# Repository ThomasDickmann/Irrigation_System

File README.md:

# Arduino Irrigation System - WIP
The purpose of this project was to learn basic electronic design, PCB layout, and embedded software development using VS code and PlatformIO.
The project is a work in progress, so use any code with appropriate caution!

Written in 2022 by Thomas Dickmann. 

## System architecture and intended use 
The goal is to create a fully automated irrigation system to be used in a home automation context. The hardware is capable of controlling two 12V pumps and four 12V solenoid valves to independently give water to up to four plants. The dual pump setup is used to create a redundant safety feature to prevent flooding upon a controller malfunction. The soil moisture level is obtained using capacitive analog sensors. Additionally, a BMP280 temperature and pressure sensor can provide ambient information. Finally, the connection of a SD card module allows for data logging and a Real Time Clock (RTC) provides time stamps and allows the system to operate in an energy efficient deep sleep state in between the service routines.     

## Content 
This repo currently contains the arduino code for the controller. The project also comprises Autodesk EAGLE files for the schematic and PCB as well as a CAD package with Fusion360 and .stl files for the various mechanical parts to put together the final product. Additionally, off-the-shelf components make up a substantial part of the system, therefore a list will be published containing links to the various components that were used. 
Finally, a manual will be created after everything is wrapped up and tested. 

### Features
+ 6 MOSFET Low side switches (LSS) with indicator LEDs for valves and motors, providing 12V input power to the peripherals 
+ PWM enabled motor control for power modulation 
+ 4 analog sensor inputs with filter capacitors 
+ High Side Switch (HSS) controlling the powering of the analog sensors and SD card (powered only when in use to reduce idle energy consumption) 
+ Data logging of soil moisture levels, temperature and air pressure with time stamps for long term observation

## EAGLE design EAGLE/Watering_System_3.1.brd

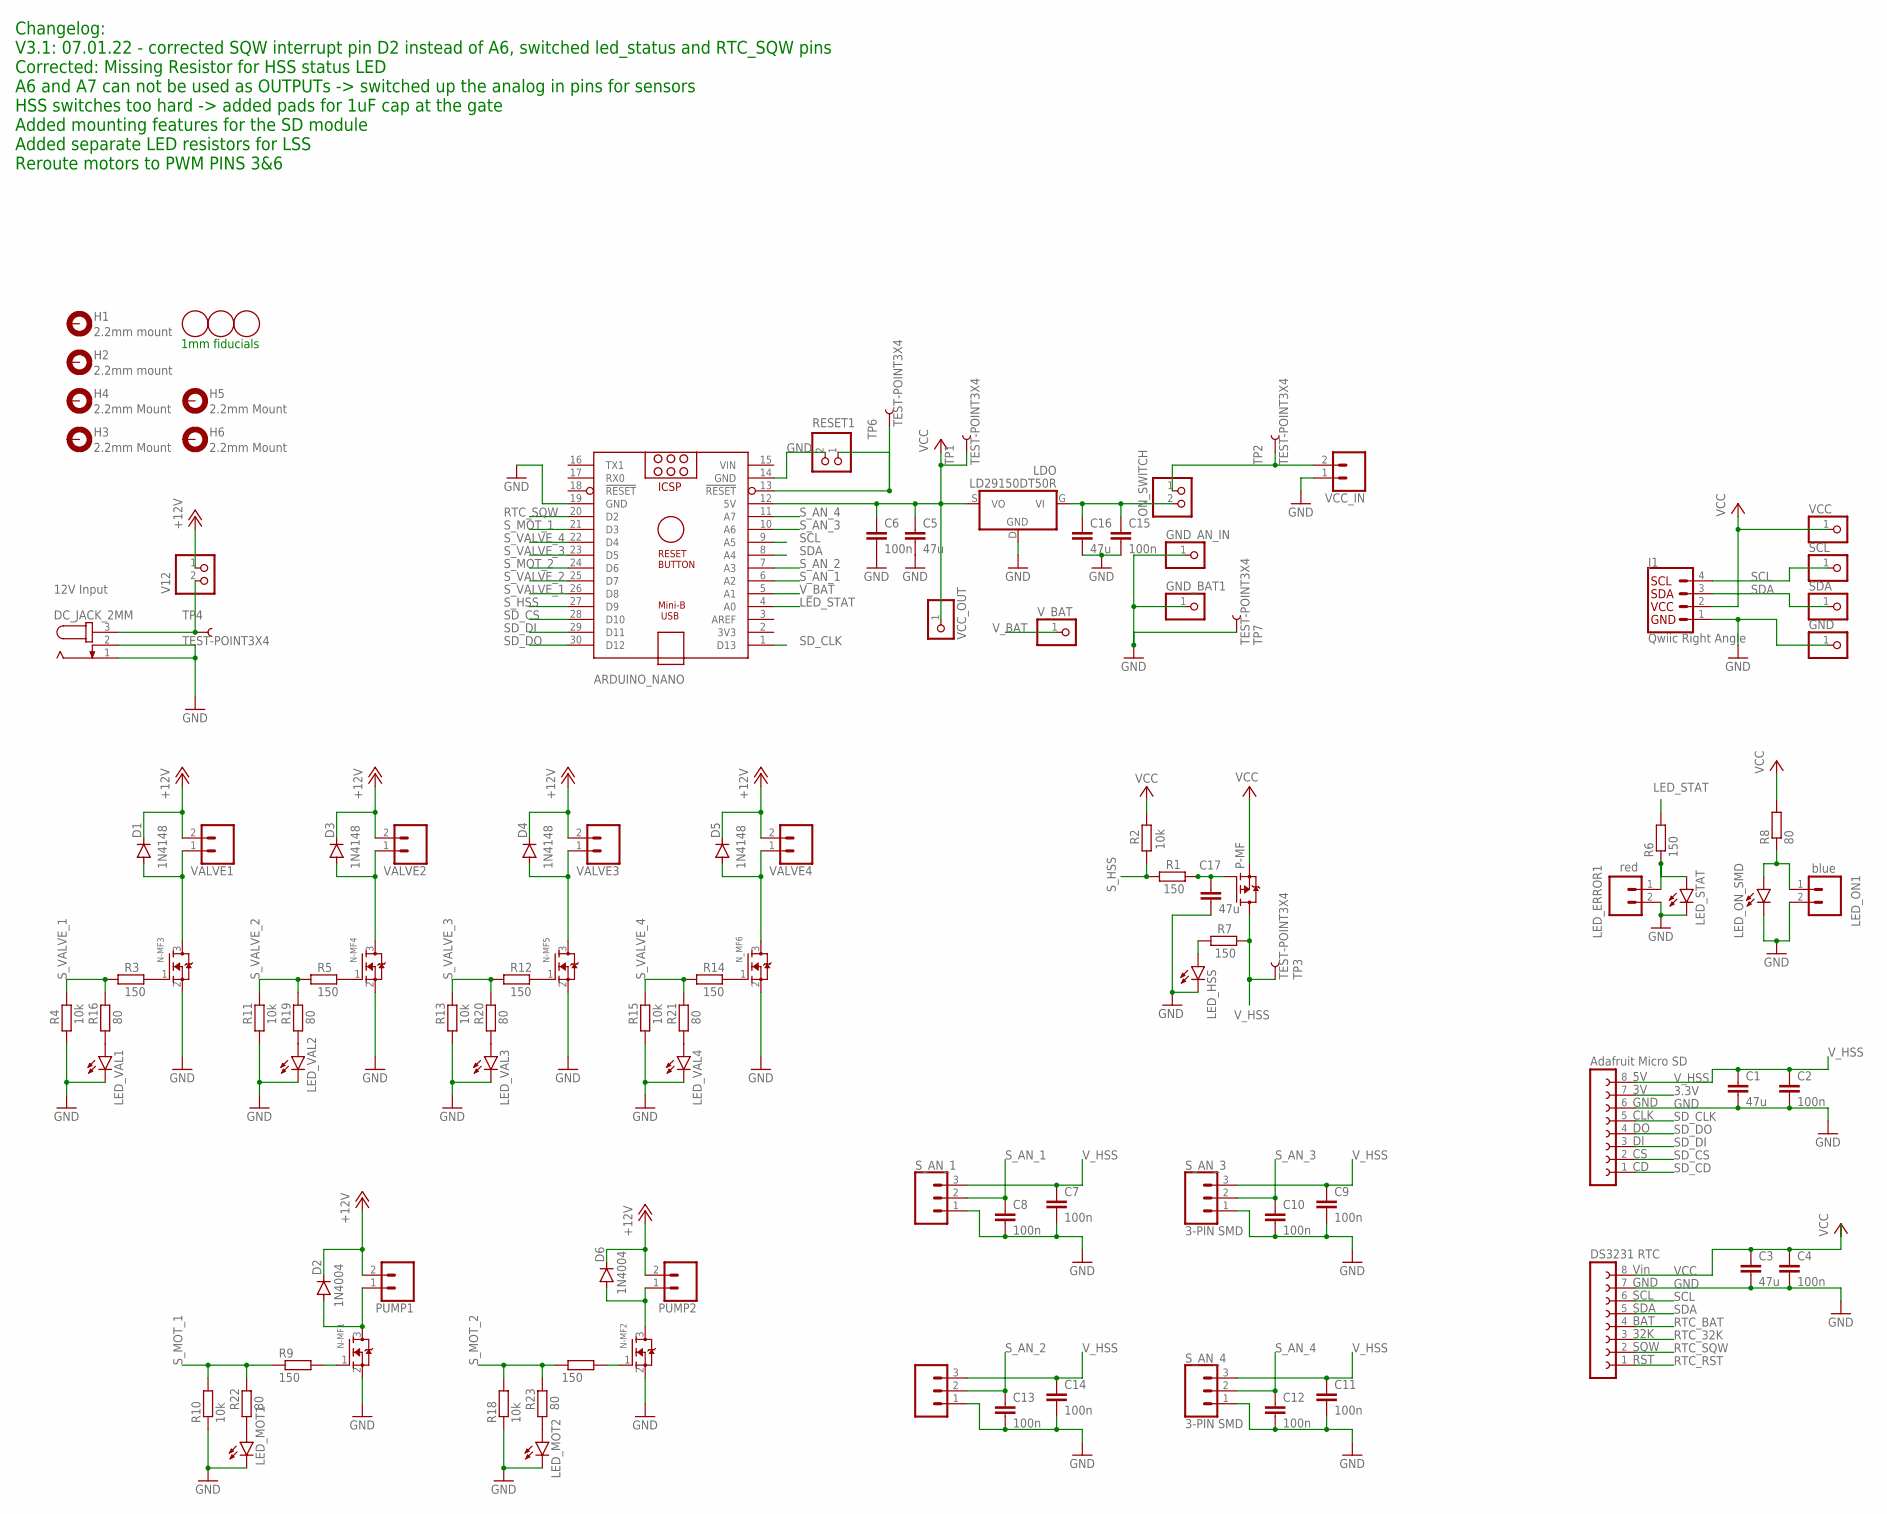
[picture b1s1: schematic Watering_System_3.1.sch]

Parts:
ARDUINO_NANO: ARDUINO_NANO
C1, C3, C5, C16, C17: 47u; C0805
C2, C4, C6, C7, C8, C9, C10, C11, C12, C13, C14, C15: 100n; C0805
D1, D3, D4, D5: 1N4148; DO35-7
D2, D6: 1N4004; DO41-10
DC_JACK_2MM: 12V Input; SPC4077
GND: PINHD-1X1; 1X01
GND_AN_IN: PINHD-1X1; 1X01
GND_BAT1: PINHD-1X1; 1X01
H1, H2: 2.2mm mount; 2,2-PAD
H3, H4, H5, H6: 2.2mm Mount; 2,2-PAD
J1: Qwiic Right Angle; 1X04_1MM_RA
LDO: LD29150DT50R; DPACK_2
LED_ERROR1: red; 1X02
LED_HSS: LEDCHIPLED_0805; CHIPLED_0805
LED_MOT1, LED_MOT2: LEDCHIPLED_0805; CHIPLED_0805
LED_ON1: blue; 1X02
LED_ON_SMD: LEDCHIPLED_0805; CHIPLED_0805
LED_STAT: LEDCHIPLED_0805; CHIPLED_0805
LED_VAL1, LED_VAL2, LED_VAL3, LED_VAL4: LEDCHIPLED_0805; CHIPLED_0805
N-MF1, N-MF2, N-MF3, N-MF4, N-MF5: IRLML6244TRPBF; SOT23R_INFINEON
N_MF6: IRLML6244TRPBF; SOT23R_INFINEON
ON_SWITCH: toggle_breakout; 1X02
P-MF: IRLML2244TRPBF; SOT23R_INFINEON
PUMP1, PUMP2: CONN_02-JST-2MM-SMT; JST-2-SMD
R1, R3, R5, R6, R7, R9, R12, R14, R17: 150; R0805
R2, R4, R10, R11, R13, R15, R18: 10k; R0805
R8, R16, R19, R20, R21, R22, R23: 80; R0805
RESET1: toggle_breakout; 1X02
RTC: DS3231; RTC
SCL: PINHD-1X1; 1X01
SC_CARD: MIRCO_SD_ADAFRUITSD; ADAFRUIT_SD
SDA: PINHD-1X1; 1X01
S_AN_1, S_AN_2, S_AN_3, S_AN_4: 3-PIN SMD; JST-3-SMD
TP1, TP2, TP3, TP4, TP6, TP7: TEST-POINT3X4; PAD.03X.04
U$1, U$2, U$3: FIDUCIAL; FIDUCIAL_1MM
V12: toggle_breakout; 1X02
VALVE1, VALVE2, VALVE3, VALVE4: CONN_02-JST-2MM-SMT; JST-2-SMD
VCC: PINHD-1X1; 1X01
VCC_IN: CONN_02-JST-2MM-SMT; JST-2-SMD
VCC_OUT: PINHD-1X1; 1X01
V_BAT: PINHD-1X1; 1X01

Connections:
3.3V: SC_CARD.7 (3V)
+12V: D1.C, D2.C, D3.C, D4.C, D5.C, D6.C, PUMP1.2 (1), PUMP2.2 (1), V12.1, VALVE1.2 (1), VALVE2.2 (1), VALVE3.2 (1), VALVE4.2 (1)
GND: ARDUINO_NANO.14 (GND), ARDUINO_NANO.19 (GND), C1.2, C2.2, C3.2, C4.2, C5.2, C6.2, C7.2, C8.2, C9.2, C10.2, C11.2, C12.2, C13.2, C14.2, C15.2, C16.2, C17.2, DC_JACK_2MM.1, DC_JACK_2MM.2, GND.1, GND_AN_IN.1, GND_BAT1.1, J1.1, LDO.D (GND), LED_ERROR1.2, LED_HSS.C, LED_MOT1.C, LED_MOT2.C, LED_ON1.2, LED_ON_SMD.C, LED_STAT.C, LED_VAL1.C, LED_VAL2.C, LED_VAL3.C, LED_VAL4.C, N-MF1.2 (S), N-MF2.2 (S), N-MF3.2 (S), N-MF4.2 (S), N-MF5.2 (S), N_MF6.2 (S), R4.1, R10.1, R11.1, R13.1, R15.1, R18.1, RESET1.2, RTC.7 (GND), SC_CARD.6 (GND), S_AN_1.1, S_AN_2.1, S_AN_3.1, S_AN_4.1, TP7.P$1, VCC_IN.1 (2)
LED_STAT: ARDUINO_NANO.4 (A0), R6.2
unnamed: N-MF1.1 (G), R9.2
unnamed: D3.A, N-MF4.3 (D), VALVE2.1 (2)
unnamed: LED_ON1.1, LED_ON_SMD.A, R8.1
unnamed: N-MF2.1 (G), R17.2
unnamed: LED_ERROR1.1, LED_STAT.A, R6.1
unnamed: LED_HSS.A, R7.1
unnamed: D1.A, N-MF3.3 (D), VALVE1.1 (2)
unnamed: N-MF4.1 (G), R5.2
unnamed: D4.A, N-MF5.3 (D), VALVE3.1 (2)
unnamed: C17.1, P-MF.1 (G), R1.2
unnamed: N-MF3.1 (G), R3.2
unnamed: N-MF5.1 (G), R12.2
unnamed: D5.A, N_MF6.3 (D), VALVE4.1 (2)
unnamed: N_MF6.1 (G), R14.2
unnamed: C15.1, C16.1, LDO.G (VI), ON_SWITCH.2
unnamed: DC_JACK_2MM.3, TP4.P$1, V12.2
unnamed: LED_VAL1.A, R16.1
unnamed: D2.A, N-MF1.3 (D), PUMP1.1 (2)
unnamed: D6.A, N-MF2.3 (D), PUMP2.1 (2)
unnamed: LED_VAL2.A, R19.1
unnamed: ARDUINO_NANO.13 (!RESET), RESET1.1, TP6.P$1
unnamed: ON_SWITCH.1, TP2.P$1, VCC_IN.2 (1)
unnamed: LED_VAL3.A, R20.1
unnamed: LED_VAL4.A, R21.1
unnamed: LED_MOT1.A, R22.1
unnamed: LED_MOT2.A, R23.1
RTC_32K: RTC.3 (32K)
RTC_BAT: RTC.4 (BAT)
RTC_RST: RTC.1 (RST)
RTC_SQW: ARDUINO_NANO.20 (D2), RTC.2 (SQW)
SCL: ARDUINO_NANO.9 (A5), J1.4, RTC.6 (SCL), SCL.1
SDA: ARDUINO_NANO.8 (A4), J1.3, RTC.5 (SDA), SDA.1
SD_CD: SC_CARD.1 (CD)
SD_CLK: ARDUINO_NANO.1 (D13), SC_CARD.5 (CLK)
SD_CS: ARDUINO_NANO.28 (D10), SC_CARD.2 (CS)
SD_DI: ARDUINO_NANO.29 (D11), SC_CARD.3 (DI)
SD_DO: ARDUINO_NANO.30 (D12), SC_CARD.4 (DO)
S_AN_1: ARDUINO_NANO.6 (A2), C8.1, S_AN_1.2
S_AN_2: ARDUINO_NANO.7 (A3), C13.1, S_AN_2.2
S_AN_3: ARDUINO_NANO.10 (A6), C10.1, S_AN_3.2
S_AN_4: ARDUINO_NANO.11 (A7), C12.1, S_AN_4.2
S_HSS: ARDUINO_NANO.27 (D9), R1.1, R2.1
S_MOT_1: ARDUINO_NANO.21 (D3), R9.1, R10.2, R22.2
S_MOT_2: ARDUINO_NANO.24 (D6), R17.1, R18.2, R23.2
S_VALVE_1: ARDUINO_NANO.26 (D8), R3.1, R4.2, R16.2
S_VALVE_2: ARDUINO_NANO.25 (D7), R5.1, R11.2, R19.2
S_VALVE_3: ARDUINO_NANO.23 (D5), R12.1, R13.2, R20.2
S_VALVE_4: ARDUINO_NANO.22 (D4), R14.1, R15.2, R21.2
VCC: ARDUINO_NANO.12 (5V), C3.1, C4.1, C5.1, C6.1, J1.2, LDO.S (VO), P-MF.2 (S), R2.2, R8.2, RTC.8 (VIN), TP1.P$1, VCC.1, VCC_OUT.1
VIN: ARDUINO_NANO.15 (VIN)
V_BAT: ARDUINO_NANO.5 (A1), V_BAT.1
V_HSS: C1.1, C2.1, C7.1, C9.1, C11.1, C14.1, P-MF.3 (D), R7.2, SC_CARD.8 (5V), S_AN_1.3, S_AN_2.3, S_AN_3.3, S_AN_4.3, TP3.P$1

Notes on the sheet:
1mm fiducials
Changelog: V3.1: 07.01.22 - corrected SQW interrupt pin D2 instead of A6, switched led_status and RTC_SQW pins Corrected: Missing Resistor for HSS status LED A6 and A7 can not be used as OUTPUTs -> switched up the analog in pins for sensors HSS switches too hard -> added pads for 1uF cap at the gat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

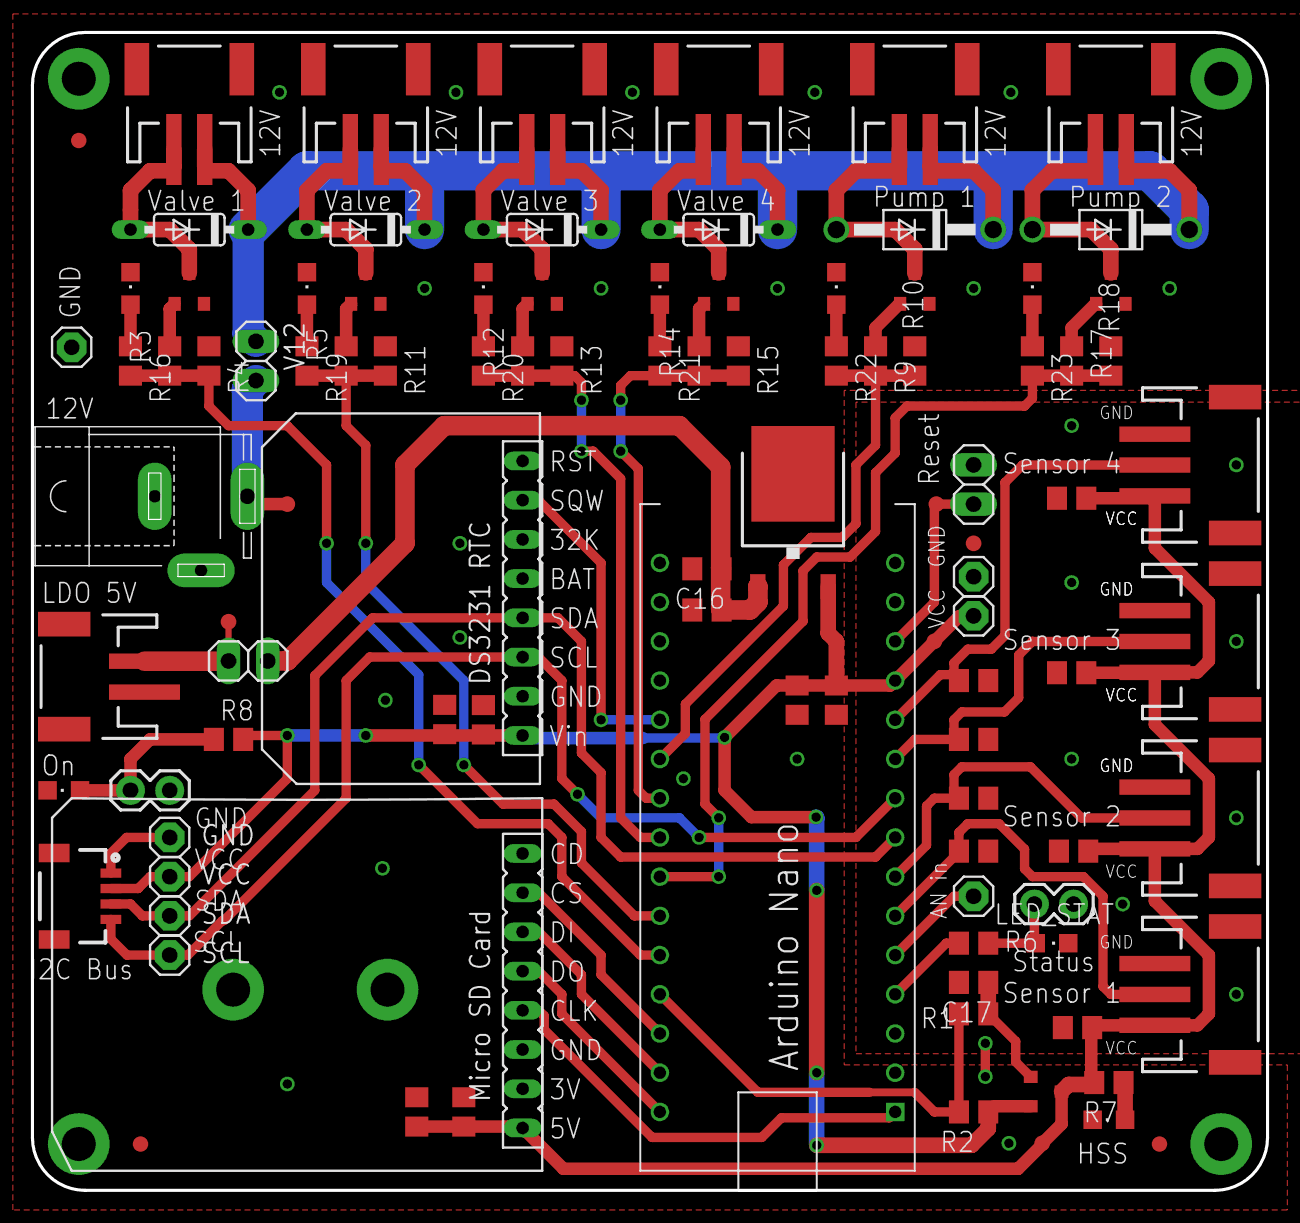
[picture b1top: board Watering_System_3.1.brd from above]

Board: 2 copper layers, 80.0 x 75.0 mm, 107 parts (0 on the bottom side), 50 nets.

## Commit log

2022-01-02 Project framework created
2022-01-02 Updated Layout
2022-01-02 Module test project added
2022-01-09 update architecture
2022-01-09 first workig setup with rtc
2022-01-12 finished variable and function distr.
2022-01-16 update service routine
2022-03-13 clean functional base for starting github workflow
2022-03-13 Rename Repo Folders
2022-03-13 Baseline for further work. Serial normal
2022-03-13 fix unsigned signed comparison error sensor data
2022-03-16 image added
2022-03-20 set up index.html file for project website
2022-03-20 test commit for public repo
2022-04-30 pcb images added
2022-04-30 add PCB layout data
2022-06-17 sync across platforms
2022-06-24 clean up variables in setup.h and setup.cpp
2022-06-24 add .DS_Store file to gitignore
2022-06-24 watering routine modified: looping over array
2022-06-24 add valve/motor check routine in setup
2022-06-24 RTC func. removed from main.cpp - bmp functional
2022-06-24 add and comment analog sensor check - sd issues
2022-06-27 sd, bmp, rtc test integration complete
2022-10-16 module test for nano, baseline for debugging firmware
2022-10-16 transition to using setup.h for variable definitions successful
2022-10-16 create object from classes successful
2022-10-16 object initialisation okay, flash and ram at 74% and 71%
2022-10-16 setup hardware check add, limit use of Serial.prin(...)
2022-10-16 add Serial.print(F(...)) everywhere -> saves RAM!
2022-10-16 sd entry add, flesh out service routine, code is functional
2022-10-23 fix sensor numbering bug, only '*' possible for String temp
2022-11-01 move system variables to setup, add object arrays
2022-11-01 functions added to setup.h/.cpp, use sd init call in main
2022-11-01 add RTC init function to setup
2022-11-01 add HSS func. to loop
2022-11-01 add soil moisture level check and watering functionality
2022-11-01 refactor main loop
2022-11-01 baseline commit - system before alarm interrupts
2022-11-01 add alarm interrupt routine, system works as intended

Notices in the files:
parts and their libraries:
SparkFun-Connectors: Licensing: Creative Commons ShareAlike 4.0 International - https://creativecommons.org/licenses/by-sa/4.0
